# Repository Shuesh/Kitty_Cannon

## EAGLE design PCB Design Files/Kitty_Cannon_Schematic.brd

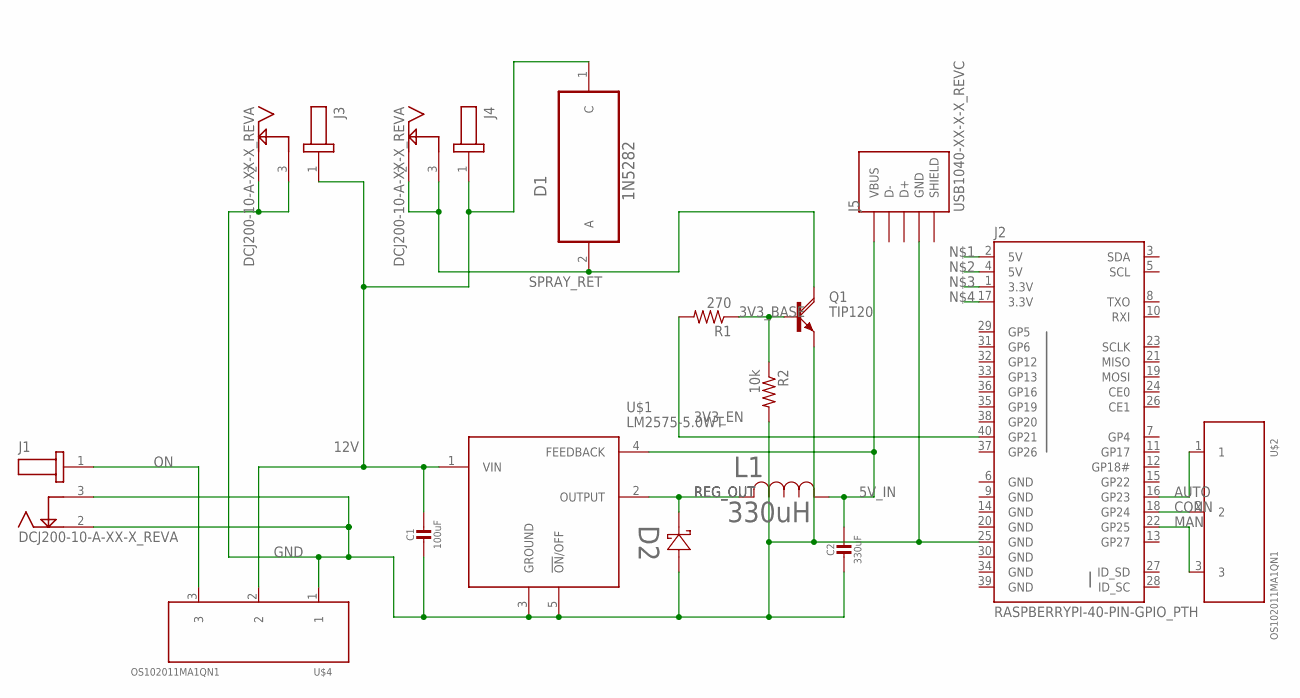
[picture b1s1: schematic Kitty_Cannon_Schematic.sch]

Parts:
C1: 100uF; 860010372006_100UF
C2: 330uF; 860010372006_100UF
D1: 1N5282; DIO_1N5282
D2: SB3100E-G; SB2E-G
J1, J3, J4: DCJ200-10-A-XX-X_REVA; GCT_DCJ200-10-A-XX-X_REVA
J2: RASPBERRYPI-40-PIN-GPIO_PTH; 2X20_SHROUDED
J5: USB1040-XX-X-X_REVC; GCT_USB1040-XX-X-X_REVC
L1: 330uH; 1433428C_MUR
Q1: TIP120; TO220AH
R1: 270; 0204/5
R2: 10k; 0204/5
U$1: LM2575-5.0WT
U$2, U$4: OS102011MA1QN1

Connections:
3V3_BASE: Q1.B, R1.1, R2.1
3V3_EN: J2.40 (GP21), R1.2
5V_IN: C2.1, J5.1 (VBUS), L1.1, U$1.4 (FEEDBACK)
12V: C1.1, D1.1 (C), J3.1, J4.1, U$1.1 (VIN), U$4.2
AUTO: J2.16 (GP23), U$2.1
CONN: J2.18 (GP24), U$2.2
GND: C1.2, C2.2, D2.2, J1.2, J1.3, J2.6 (GND), J2.9 (GND), J2.14 (GND), J2.20 (GND), J2.25 (GND), J2.30 (GND), J2.34 (GND), J2.39 (GND), J3.2, J3.3, J5.4 (GND), Q1.E, R2.2, U$1.3 (GROUND), U$1.5 (!ON!/OFF), U$4.1
MAN: J2.22 (GP25), U$2.3
ON: J1.1, U$4.3
REG_OUT: D2.1, L1.2, U$1.2 (OUTPUT)
SHIELD: J5.5 (SHIELD), J5.6 (SHIELD)
SPRAY_RET: D1.2 (A), J4.2, J4.3, Q1.C

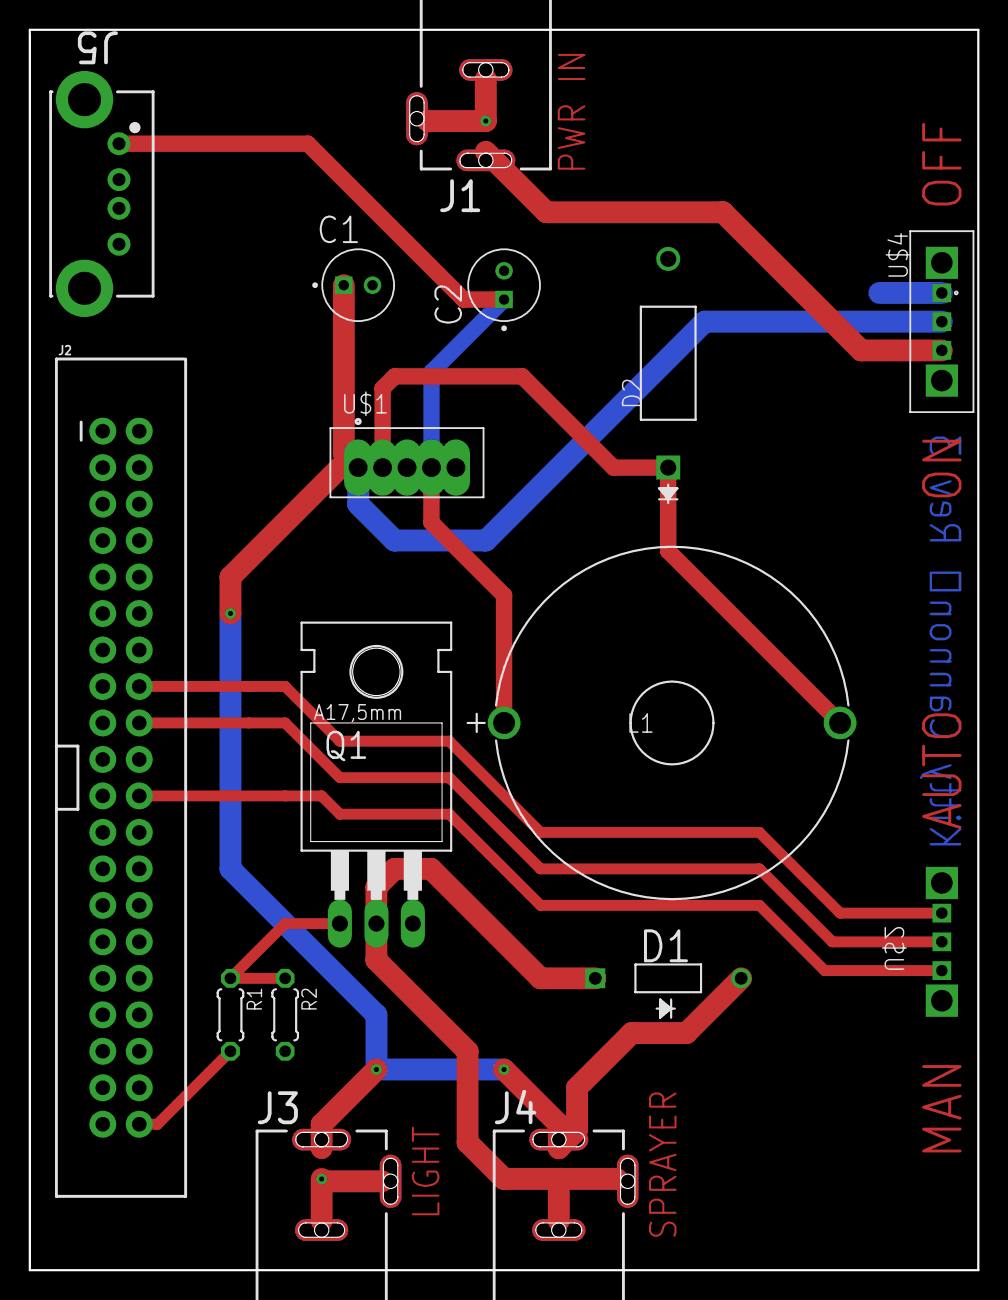
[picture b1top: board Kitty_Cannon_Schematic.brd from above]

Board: 2 copper layers, 66.0 x 86.4 mm, 16 parts (1 on the bottom side), 12 nets.

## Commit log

2021-02-18 Main creation
2021-02-18 Adding requirements.txt
2021-02-18 added import opencv
2021-02-18 Main skeleton
2021-02-18 Adding config
2021-05-15 servo pwm, changes to requirements, added to init
2021-07-13 Add component notes
2021-08-14 More polished GUI and some work done on Main.py
2021-08-28 Polished interface, just started implementing JavaScript.
2021-08-28 Additional Files
2021-09-28 Eagle Project Files
2021-12-05 Kitty Cannon - update structure
2021-12-05 remove rdp file
2021-12-05 Reorganizing
2022-03-21 Update to track cat faces and not humans
2022-07-22 Updated html, added svgs and refactored css
2022-07-22 Transition to flask framework as it's running on rpi
2022-07-22 update to script.js position and link in html
2022-07-22 alter js location
2022-07-22 reposition js
2022-07-23 Edit to use AJAX for passing button commands to Flask
2022-07-23 Tried rearranging some things
2022-07-23 Working Flask and JS connection
2022-07-23 Minor changes to camera.py
2022-07-23 Beginning image processing and manual control. Reorganized haar cascades
2022-07-26 Working gpio_interface and manual modules
2022-07-26 Frontend to servo positioning pipeline complete - Manual

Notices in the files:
parts and their libraries:
SparkFun-Connectors: Licensing: Creative Commons ShareAlike 4.0 International - https://creativecommons.org/licenses/by-sa/4.0
COPYRIGHT: Copyright (C) 2021 Ultra Librarian. All rights reserved.
